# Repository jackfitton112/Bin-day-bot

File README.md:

# Bin Day Bot

Bin Day bot is a simple bot that will remind you when to put your bins out. On Binday it will glow the colour of the bin you need to put out. It will also remind you the night before.

The PCB is designed to fit into [This model by BrewStew](https://www.thingiverse.com/thing:3377785). 

Currently it only works on the York City Council waste API but I am working on making it more universal.

## Software

To be added when PCBs arrive.

---
### License

Software is licensed under the [CC-BY-SA-4.0 license](https://creativecommons.org/licenses/by-sa/4.0/).

Hardware is licensed under the CERN Open Hardware Licence v1.2 - see the [LICENSE.md](LICENSE.md) file for details. This complies with the requirements of the [Open Source Hardware Association](https://www.oshwa.org/definition/).

Documentation is licensed under the [CC-BY-SA-4.0 license](https://creativecommons.org/licenses/by-sa/4.0/).

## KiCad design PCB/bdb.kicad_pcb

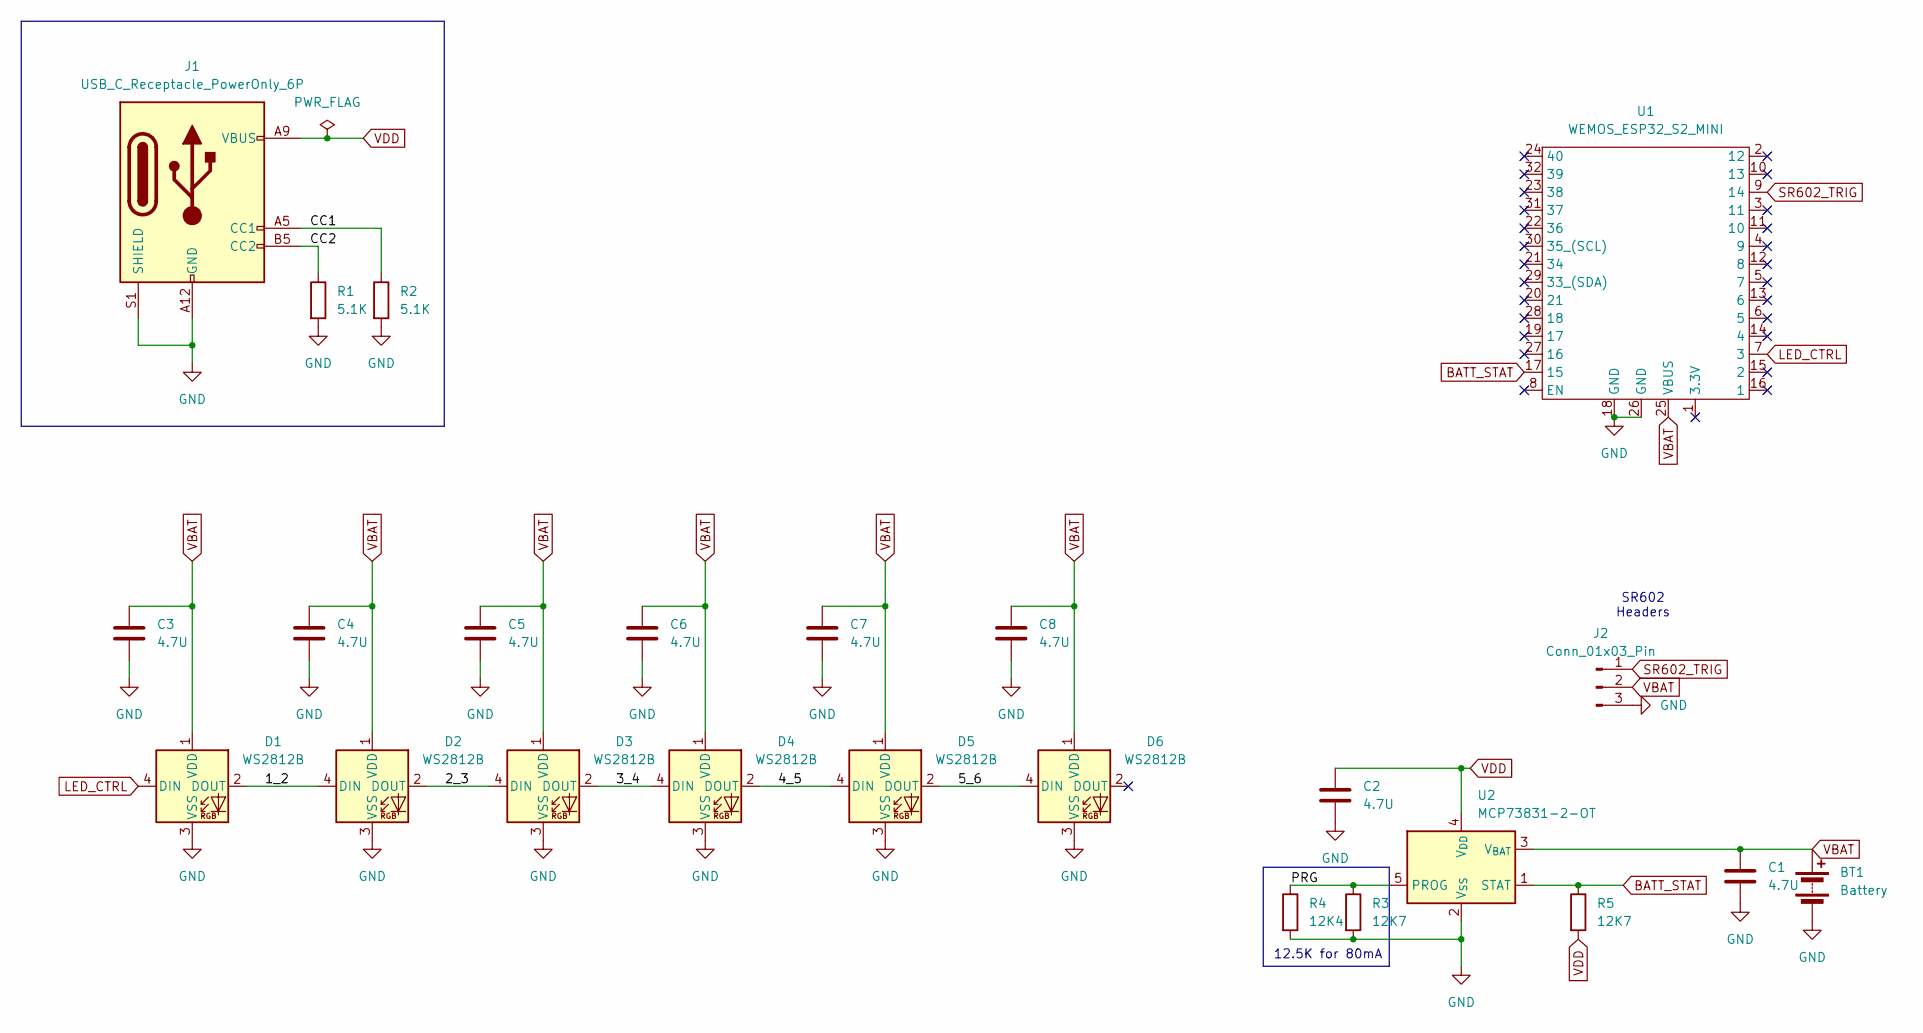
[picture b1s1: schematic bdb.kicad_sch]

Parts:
BT1: Battery; JST_PH_S2B-PH-K_1x02_P2.00mm_Horizontal
C1, C2, C3, C4, C5, C6, C7, C8: 4.7U; C_0603_1608Metric_Pad1.08x0.95mm_HandSolder
D1, D2, D3, D4, D5, D6: WS2812B; LED_WS2812B_PLCC4_5.0x5.0mm_P3.2mm
J1: USB_C_Receptacle_PowerOnly_6P; USB_C_Receptacle_GCT_USB4125-xx-x-0190_6P_TopMnt_Horizontal
J2: Conn_01x03_Pin; PinHeader_1x03_P2.54mm_Vertical
R1, R2: 5.1K; R_0603_1608Metric_Pad0.98x0.95mm_HandSolder
R3, R5: 12K7; R_0603_1608Metric_Pad0.98x0.95mm_HandSolder
R4: 12K4; R_0603_1608Metric_Pad0.98x0.95mm_HandSolder
U1: WEMOS_ESP32_S2_MINI
U2: MCP73831-2-OT; SOT-23-5

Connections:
/1_2: D1.2 (DOUT), D2.4 (DIN)
/2_3: D2.2 (DOUT), D3.4 (DIN)
/3_4: D3.2 (DOUT), D4.4 (DIN)
/4_5: D4.2 (DOUT), D5.4 (DIN)
/5_6: D5.2 (DOUT), D6.4 (DIN)
/CC1: J1.A5 (CC1), R2.1
/CC2: J1.B5 (CC2), R1.1
/PRG: R3.1, R4.1, U2.5 (PROG)
BATT_STAT: R5.1, U1.17 (15), U2.1 (STAT)
GND: BT1.2 (-), C1.2, C2.2, C3.2, C4.2, C5.2, C6.2, C7.2, C8.2, D1.3 (VSS), D2.3 (VSS), D3.3 (VSS), D4.3 (VSS), D5.3 (VSS), D6.3 (VSS), J1.A12 (GND), J1.B12 (GND), J1.S1 (SHIELD), J2.3, R1.2, R2.2, R3.2, R4.2, U1.18 (GND), U1.26 (GND), U2.2 (V_{SS})
LED_CTRL: D1.4 (DIN), U1.7 (3)
SR602_TRIG: J2.1, U1.9 (14)
VBAT: BT1.1 (+), C1.1, C3.1, C4.1, C5.1, C6.1, C7.1, C8.1, D1.1 (VDD), D2.1 (VDD), D3.1 (VDD), D4.1 (VDD), D5.1 (VDD), D6.1 (VDD), J2.2, U1.25 (VBUS), U2.3 (V_{BAT})
VDD: C2.1, J1.A9 (VBUS), J1.B9 (VBUS), R5.2, U2.4 (V_{DD})

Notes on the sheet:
12.5K for 80mA
SR602 Headers

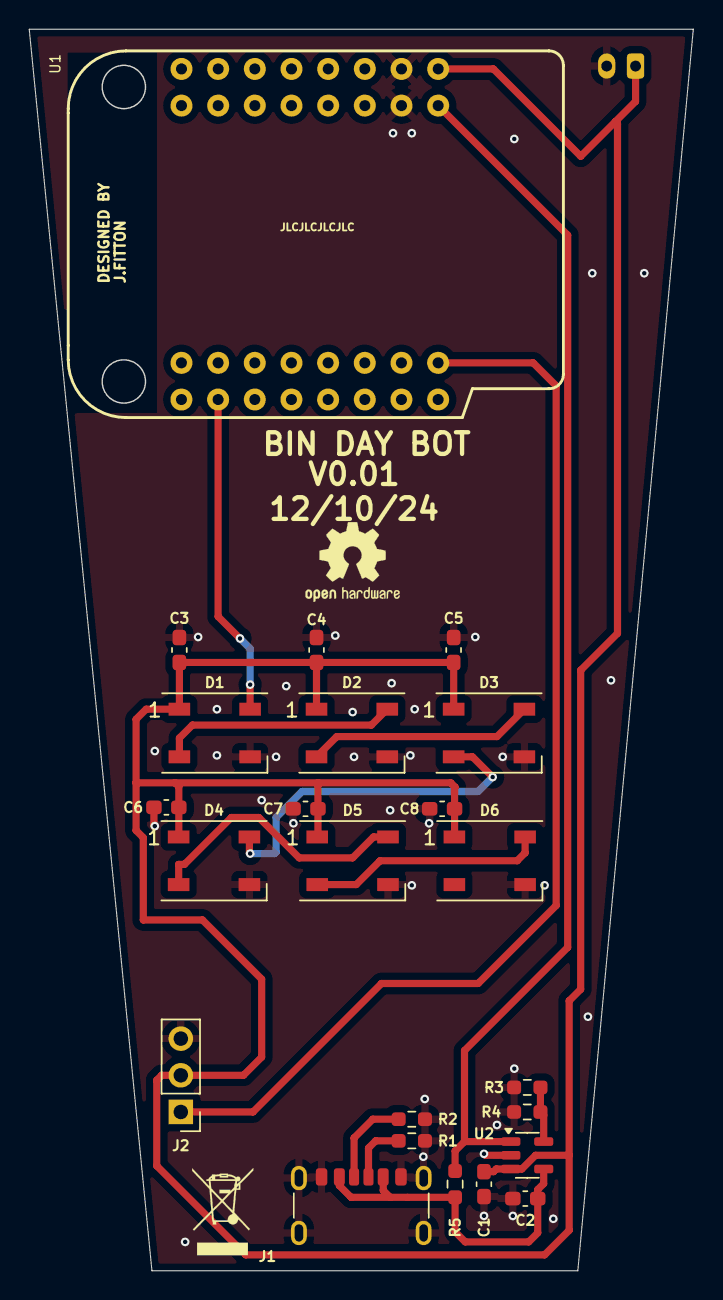
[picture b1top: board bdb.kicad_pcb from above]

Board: 2 copper layers, 46.0 x 85.9 mm, 24 parts (1 on the bottom side), 14 nets.

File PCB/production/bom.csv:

Designator,Footprint,Quantity,Value,LCSC Part #
BT1,JST_PH_S2B-PH-K_1x02_P2.00mm_Horizontal,1,Battery,
"C1, C2, C3, C4, C5, C6, C7, C8",0603,8,4.7U,
"D1, D2, D3, D4, D5, D6",LED_WS2812B_PLCC4_5.0x5.0mm_P3.2mm,6,WS2812B,
J1,USB_C_Receptacle_GCT_USB4125-xx-x-0190_6P_TopMnt_Horizontal,1,USB_C_Receptacle_PowerOnly_6P,
J2,PinHeader_1x03_P2.54mm_Vertical,1,Conn_01x03_Pin,
"R1, R2",0603,2,5.1K,
"R3, R5",0603,2,12K7,
R4,0603,1,12K4,
U1,WEMOS_ESP32_S2_MINI,1,WEMOS_ESP32_S2_MINI,
U2,SOT-23-5,1,MCP73831-2-OT,

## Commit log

2024-10-12 updated licenense to GPL
2024-10-12 updated license to CERN OHW
